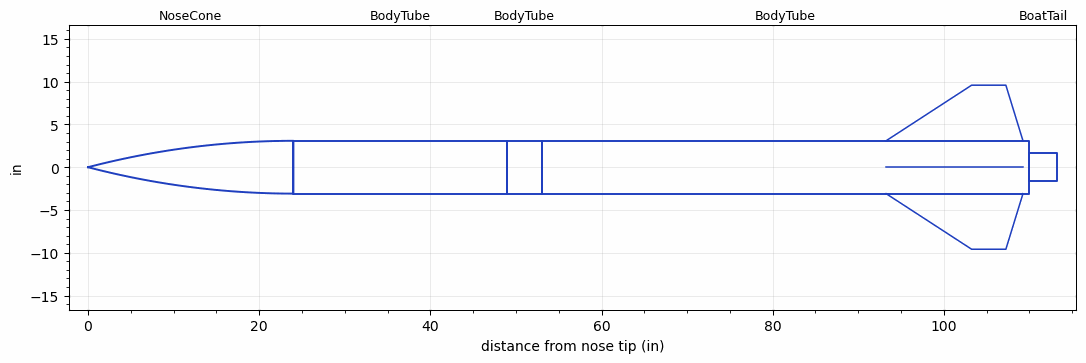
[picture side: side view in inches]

<RASAeroDocument>
 <FileVersion>2</FileVersion>
 <RocketDesign>
  <NoseCone>
   <Length>24</Length>
   <Diameter>6.17</Diameter>
   <Shape>Tangent Ogive</Shape>
   <Location>0</Location>
  </NoseCone>
  <BodyTube>
   <Length>24.9999</Length>
   <Diameter>6.17</Diameter>
   <Location>24</Location>
  </BodyTube>
  <BodyTube>
   <Length>4</Length>
   <Diameter>6.17</Diameter>
   <Location>48.9999</Location>
  </BodyTube>
  <BodyTube>
   <Length>56.9999</Length>
   <Diameter>6.17</Diameter>
   <RailGuideDiameter>0.49</RailGuideDiameter>
   <RailGuideHeight>0.56</RailGuideHeight>
   <Location>52.9999</Location>
   <Fin>
    <Count>4</Count>
    <Chord>16</Chord>
    <Span>6.5</Span>
    <SweepDistance>10</SweepDistance>
    <TipChord>4</TipChord>
    <Thickness>0.1875</Thickness>
    <Location>16.75</Location>
    <AirfoilSection>Rounded</AirfoilSection>
   </Fin>
  </BodyTube>
  <BoatTail>
   <Length>3.1991</Length>
   <Diameter>3.2546</Diameter>
   <RearDiameter>3.2546</RearDiameter>
   <Location>109.9998</Location>
  </BoatTail>
  <Surface>Camouflage Paint</Surface>
  <CD>0</CD>
  <ModifiedBarrowman>False</ModifiedBarrowman>
  <Turbulence>False</Turbulence>
  <UseBooster1>False</UseBooster1>
  <UseBooster2>False</UseBooster2>
 </RocketDesign>
 <LaunchSite>
  <Altitude>2920.0001</Altitude>
  <Pressure>26.9029</Pressure>
  <RodAngle>6</RodAngle>
  <RodLength>15.2559</RodLength>
  <Temperature>85</Temperature>
  <WindSpeed>0</WindSpeed>
 </LaunchSite>
 <Recovery>
  <Altitude1>656.168</Altitude1>
  <Altitude2>1000</Altitude2>
  <DeviceType1>Parachute</DeviceType1>
  <DeviceType2>Parachute</DeviceType2>
  <Event1>True</Event1>
  <Event2>True</Event2>
  <Size1>35.9999</Size1>
  <Size2>167.9997</Size2>
  <EventType1>Apogee</EventType1>
  <EventType2>Altitude</EventType2>
  <CD1>0.97</CD1>
  <CD2>0</CD2>
 </Recovery>
 <SimulationList>
  <Simulation>
   <SustainerEngine>M2000R  (AT)</SustainerEngine>
   <SustainerLaunchWt>64.9298</SustainerLaunchWt>
   <SustainerCG>67.3231</SustainerCG>
   <SustainerIgnitionDelay>0</SustainerIgnitionDelay>
   <Booster1SeparationDelay>0</Booster1SeparationDelay>
   <Booster1IgnitionDelay>0</Booster1IgnitionDelay>
   <IncludeBooster1>False</IncludeBooster1>
   <Booster2Delay>0</Booster2Delay>
   <IncludeBooster2>False</IncludeBooster2>
  </Simulation>
 </SimulationList>
</RASAeroDocument>
